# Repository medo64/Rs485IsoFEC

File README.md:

[Isolated RS-485 Framework Expansion Card](https://medo64.com/rs485isofec/)
===========================================================================

This Framework laptop expansion card will show up on your system as a serial
device and allow for isolated RS-485 communication up to 460,800 baud rate.

Please note that this card is using automatic transmit control and 120Ω
termination.

## Pinout

To connect to this board, one has to use a 4-pin JST XH connector. The following
table represents the pinout, pin 1 being on the left as looking into the
expansion card.

| # | Ref | Description                                     |
|--:|-----|-------------------------------------------------|
| 1 | GND | Ground connection                               |
| 2 | A   | Negative (low for logic 1 and high for logic 0) |
| 3 | B   | Positive (high for logic 1 and low for logic 0) |
| 4 | NC  | Not connected                                   |

As power consumption is low, wires can be almost any AWG. I would recommend
using 24 AWG wire 0.25 mm² as they allow for greater compatibility with other
connectors.

## Supported Speeds

This board employs the FT232R as its UART chip, and consequently, it supports
all the baud rates this chip [can handle](https://ftdichip.com/Documents/AppNotes/AN232B-05_BaudRates.pdf)
up to 500,000 baud which is the limit of isolator chip used. The table below
lists the standard baud rates.

| Baud rate |    Actual | Error |    Divisor |
|----------:|----------:|------:|-----------:|
|       300 |       300 | 0.00% |  10000.000 |
|       600 |       600 | 0.00% |   5000.000 |
|     1,200 |     1,200 | 0.00% |   2500.000 |
|     1,800 |     1,800 | 0.00% |   1666.625 |
|     2,400 |     2,400 | 0.00% |   1250.000 |
|     4,800 |     4,800 | 0.00% |    625.000 |
|     7,200 |     7,201 | 0.01% |    416.625 |
|     9,600 |     9,600 | 0.00% |    312.500 |
|    14,400 |    14,406 | 0.04% |    208.250 |
|    19,200 |    19,200 | 0.00% |    156.250 |
|    28,800 |    28,812 | 0.04% |    104.125 |
|    38,400 |    38,400 | 0.00% |     78.125 |
|    57,600 |    57,692 | 0.16% |     52.000 |
|   115,200 |   115,385 | 0.16% |     26.000 |
|   230,400 |   230,769 | 0.16% |     13.000 |
|   460,800 |   461,538 | 0.16% |      6.500 |

While rates above this can be set, they are not guaranteed to work.

---
*You can check my blog and other projects at [www.medo64.com](https://www.medo64.com/electronics/).*

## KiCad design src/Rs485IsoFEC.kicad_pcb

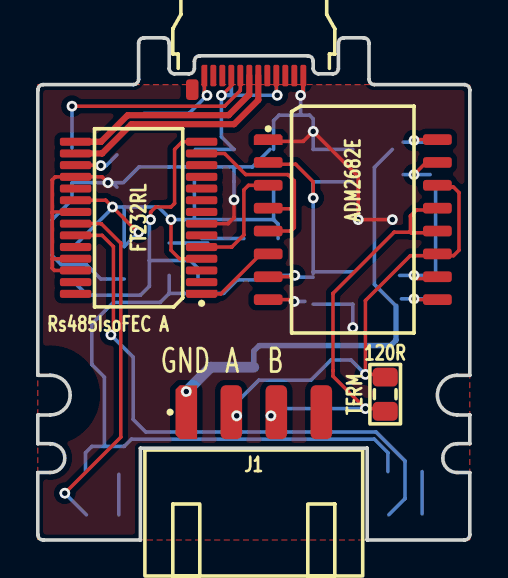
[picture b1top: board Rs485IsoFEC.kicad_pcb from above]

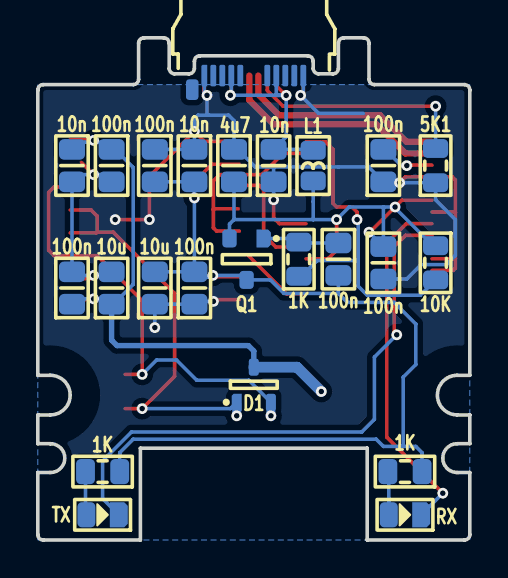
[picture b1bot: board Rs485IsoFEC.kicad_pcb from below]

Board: 2 copper layers, 24.0 x 27.9 mm, 28 parts (23 on the bottom side), 21 nets.

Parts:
C1, C2, C3: 10n; C (0805)
C4, C5, C6, C7, C8, C9, C10: 100n; C (0805)
C11: 4u7; C (0805)
C12, C13: 10u; C (0805)
D1: SM12T1G; D TVS SM05T1G (SOT23-3)
DS1: RX; DS (0805)
DS2: TX; DS (0805)
J1: B4B-XH-A; J JST XH Edge [RS485] (4w)
L1: 600R; L (0805)
P1: 105444-0001; P USB C 3.2 Edge (24w)
Q1: DMP3099L-13; Q MOSFET-P (SOT23-3)
R1: 120R; R (0805)
R2, R3, R4: 1K; R (0805)
R5: 10K; R (0805)
R5#2: 5K1; R (0805)
U1: FT232RL; U Transciever UART FT232RL (SSOP-28)
U2: ADM2682E; U Transciever RS485 Isolated ADM2682E (SOIC-16)

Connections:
3V3: C5.2, U1.17
5V: C4.2, C11.2, L1.1, Q1.2, R5.1, U1.4, U1.20
5V_SW: C2.2, C6.2, C7.2, C9.2, C12.2, Q1.3, R2.1, R3.1, U2.2, U2.7
A_CC: P1.A5, R5#2.2
GND: C1.1, C2.1, C4.1, C5.1, C7.1, C9.1, C11.1, C12.1, P1.A1, P1.A12, P1.B01, P1.B12, R5#2.1, U1.7, U1.18, U1.21, U1.25, U1.26, U2.1, U2.8
ISO_A: D1.2, J1.2, R1.1, U2.11, U2.14
ISO_B: D1.1, J1.3, R1.2, U2.12, U2.13
ISO_GND: C3.1, C8.1, C10.1, C13.1, D1.3, J1.1, U2.9, U2.16
ISO_V+: C3.2, C8.2, C10.2, C13.2, U2.10, U2.15
LED_RXD: DS1.1, U1.22
LED_RXD': DS1.2, R2.2
LED_TXD: DS2.1, U1.23
LED_TXD': DS2.2, R3.2
PWREN#: R4.1, R5.2, U1.14
PWREN#': C6.1, Q1.1, R4.2
RXD: U1.5, U2.3
TXD: U1.1, U2.6
TXDEN: U1.13, U2.4, U2.5
USB_DM: P1.A7, U1.16
USB_DP: P1.A6, U1.15
USB_Vin: C1.2, L1.2, P1.A4, P1.A9, P1.B04, P1.B09

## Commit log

2023-11-13 Removed fail-safe termination
2023-11-13 Refactoring traces a bit + renaming termination resistor
2023-11-13 Fixed half-duplex RS-485
2023-11-13 Refactoring isolator orientation
2023-11-13 Moving LEDs to bottom
2023-11-13 Moved termination resistor
2023-12-26 Added PWREN pullup and moved LED 5V to switched
2023-12-26 Aligned resistors
2023-12-26 Removed internal RTS/CTS connection
2023-12-26 Renamed FT_PRog template file
2023-12-29 Updated connector to solder all 4 pins
2023-12-30 Refactoring copper pour
2024-01-31 Moved board RefDes to top
